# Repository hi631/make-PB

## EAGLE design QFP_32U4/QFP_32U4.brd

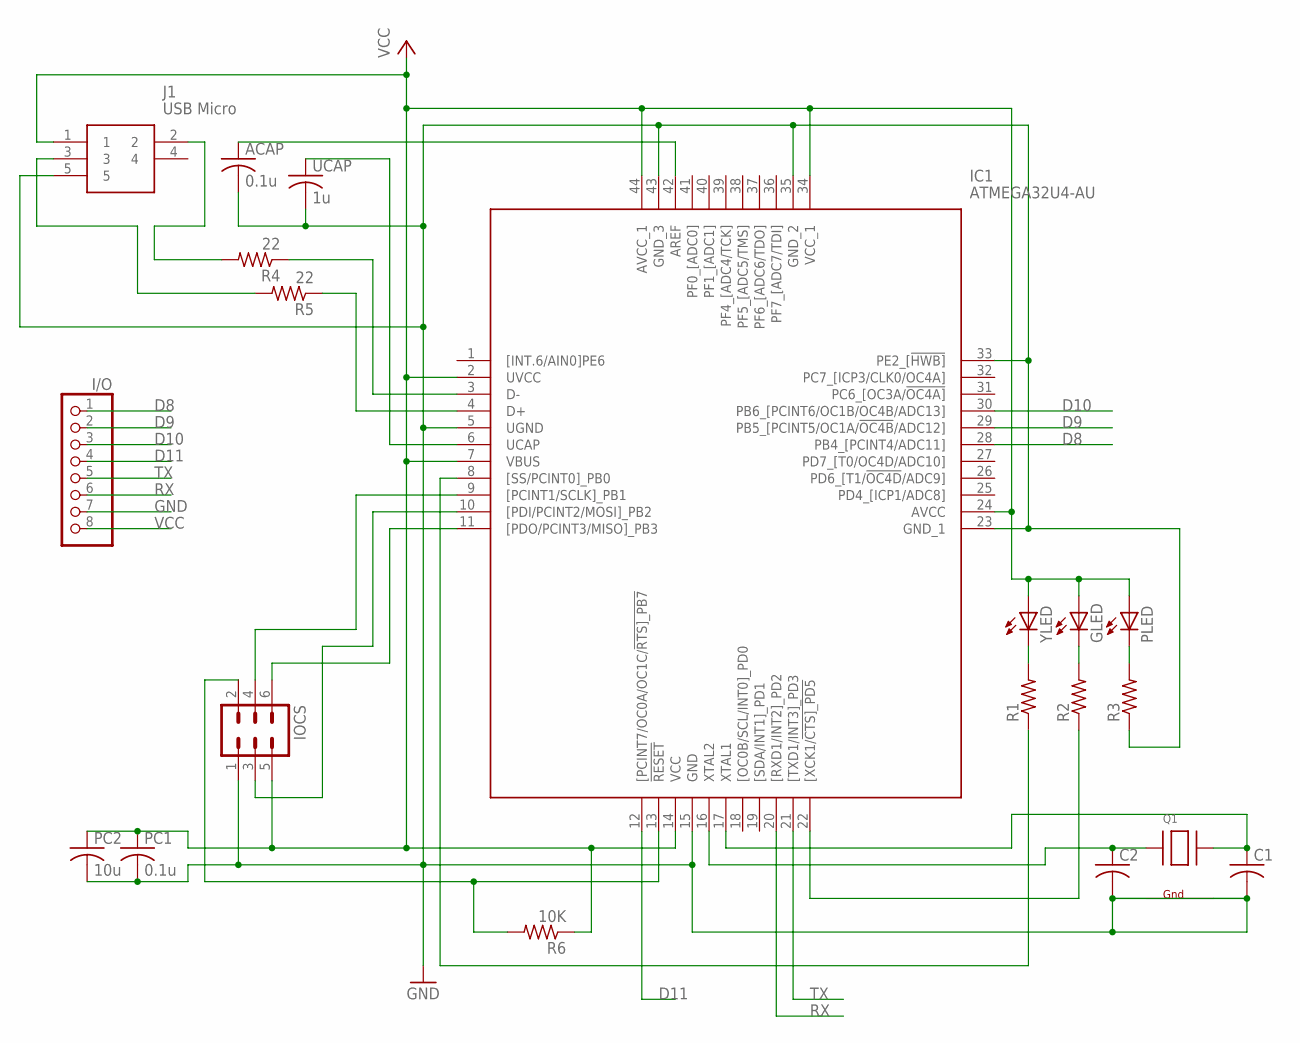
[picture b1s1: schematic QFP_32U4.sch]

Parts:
ACAP: 0.1u; C0805
C1, C2: C-USC0805; C0805
GLED: LEDCHIP-LED0805; CHIP-LED0805
I/O: PINHD-1X8CLEANBIG; 1X08-CLEANBIG
IC1: ATMEGA32U4-AU; QFP80P1200X1200X120-44N
IOCS: MA03-2
J1: USB Micro; 10104110-0001LF
PC1: 0.1u; C0805
PC2: 10u; C0805
PLED: LEDCHIP-LED0805; CHIP-LED0805
Q1: XTAL-4-3225; NX3225
R1, R2, R3: R-US_M0805; M0805
R4, R5: 22; M0805
R6: 10K; M0805
UCAP: 1u; C0805
YLED: LEDCHIP-LED0805; CHIP-LED0805

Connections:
D8: I/O.1, IC1.28 (PB4_[PCINT4/ADC11])
D9: I/O.2, IC1.29 (PB5_[PCINT5/OC1A/!OC4B!/ADC12])
D10: I/O.3, IC1.30 (PB6_[PCINT6/OC1B/OC4B/ADC13])
D11: I/O.4, IC1.12 ([PCINT7/OC0A/OC1C/!RTS]_PB7)
GND: ACAP.2, C1.2, C2.2, I/O.7, IC1.5 (UGND), IC1.15 (GND), IC1.23 (GND_1), IC1.33 (PE2_[!HWB]), IC1.35 (GND_2), IC1.43 (GND_3), IOCS.1, J1.5, PC1.2, PC2.2, Q1.2 (G2), Q1.4 (G1), R3.1, UCAP.2
unnamed: IC1.3 (D-), R4.1
unnamed: IC1.4 (D+), R5.1
unnamed: J1.2, R4.2
unnamed: IC1.6 (UCAP), UCAP.1
unnamed: R1.2, YLED.C
unnamed: IC1.8 ([SS/PCINT0]_PB0), R1.1
unnamed: IC1.9 ([PCINT1/SCLK]_PB1), IOCS.4
unnamed: IC1.10 ([PDI/PCINT2/MOSI]_PB2), IOCS.3
unnamed: IC1.11 ([PDO/PCINT3/MISO]_PB3), IOCS.6
unnamed: IC1.13 (!RESET), IOCS.2, R6.2
unnamed: J1.3, R5.2
unnamed: GLED.C, R2.2
unnamed: C2.1, IC1.16 (XTAL2), Q1.1 (X1)
unnamed: IC1.22 ([XCK1/!CTS]_PD5), R2.1
unnamed: PLED.C, R3.2
unnamed: C1.1, IC1.17 (XTAL1), Q1.3 (X2)
unnamed: ACAP.1, IC1.42 (AREF)
RX: I/O.6, IC1.20 ([RXD1/INT2]_PD2)
TX: I/O.5, IC1.21 ([TXD1/INT3]_PD3)
VCC: GLED.A, I/O.8, IC1.2 (UVCC), IC1.7 (VBUS), IC1.14 (VCC), IC1.24 (AVCC), IC1.34 (VCC_1), IC1.44 (AVCC_1), IOCS.5, J1.1, PC1.1, PC2.1, PLED.A, R6.1, YLED.A

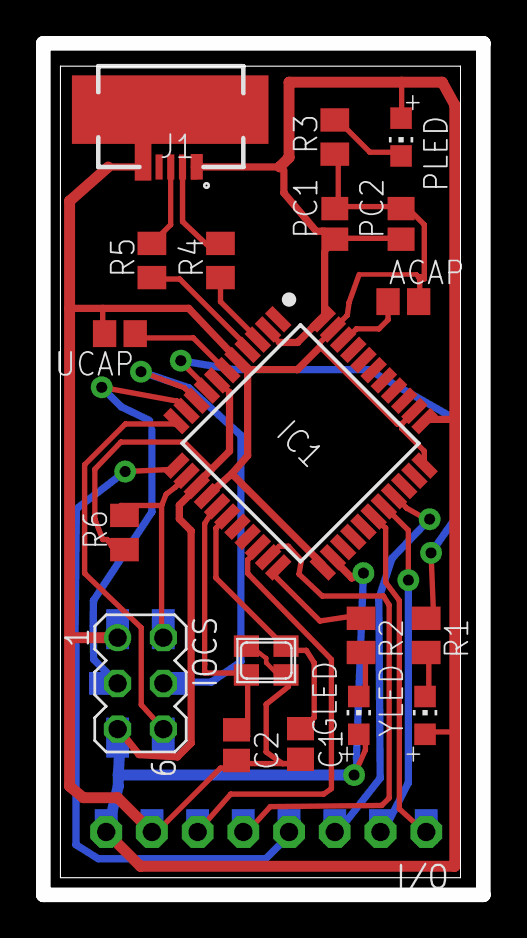
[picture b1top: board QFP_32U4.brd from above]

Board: 2 copper layers, 24.4 x 47.3 mm, 20 parts (0 on the bottom side), 25 nets.

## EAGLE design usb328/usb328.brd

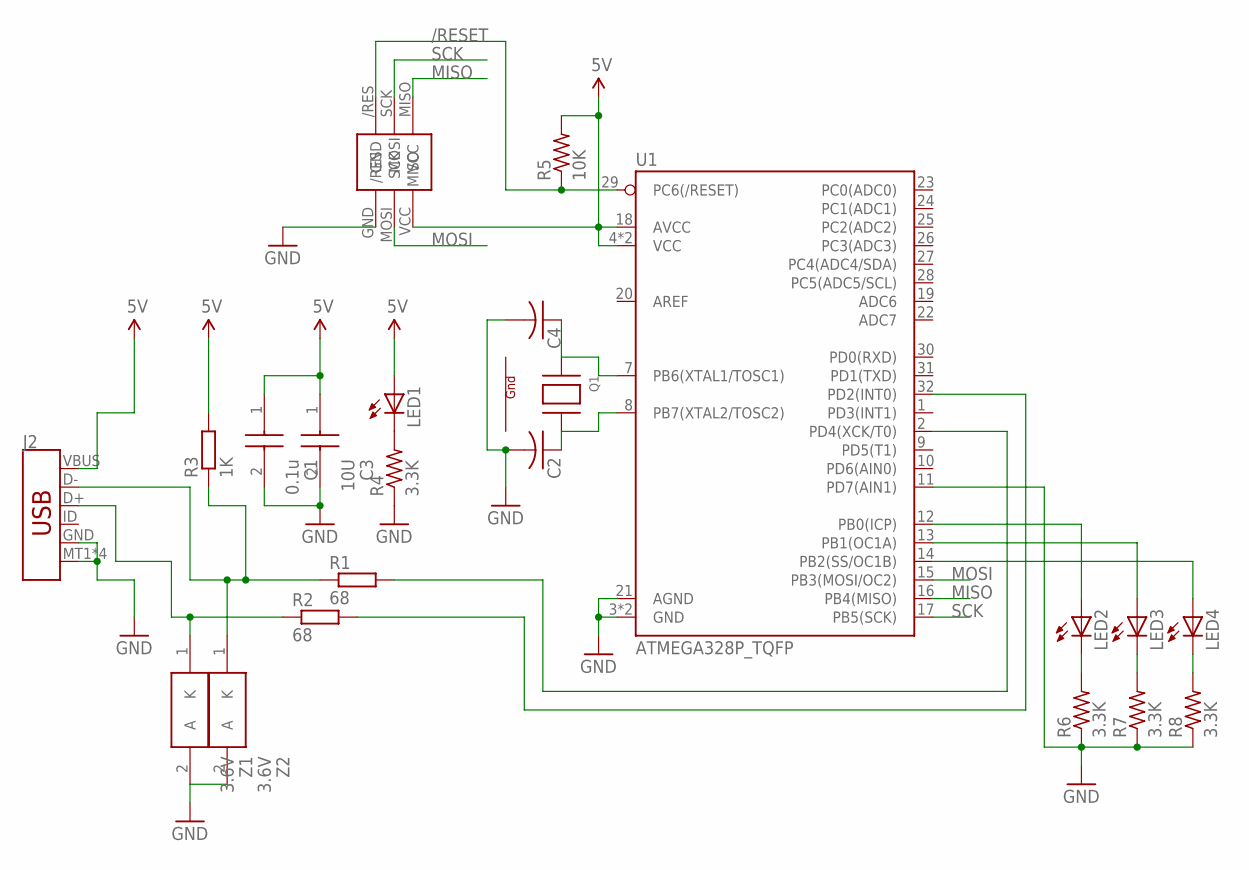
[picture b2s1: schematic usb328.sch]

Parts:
C1: 0.1u; CAPC2012X70N
C2, C4: C-USC0805; C0805
C3: 10U; CAPC2012X70N
J2: USB_MICRO-B_SMT; USB-MICROB
LED1, LED2, LED3, LED4: LEDCHIPLED_0805; CHIPLED_0805
Q1: XTAL-4-3225; NX3225
R1, R2: 68; R2012
R3: 1K; R2012
R4, R6, R7, R8: 3.3K; R0805
R5: 10K; R0805
U1: ATMEGA328P_TQFP; TQFP32-08
U$4: ICSP-E
Z1, Z2: 3.6V; TUM-D2

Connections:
5V: C1.1, C3.1, J2.VBUS, LED1.A, R3.2, R5.2, U1.4 (VCC), U1.6 (VCC), U1.18 (AVCC), U$4.VCC
/RESET: R5.1, U1.29 (PC6(/RESET)), U$4./RES
G1: Q1.4 (G1)
G2: Q1.2 (G2)
GND: C1.2, C2.2, C3.2, C4.2, J2.GND, J2.MT1 (SHIELD), J2.MT2 (SHIELD), J2.P$1 (SHIELD), J2.P$2 (SHIELD), R4.1, R6.1, R7.1, R8.1, U1.3 (GND), U1.5 (GND), U1.11 (PD7(AIN1)), U1.21 (AGND), U$4.GND, Z1.2 (A), Z2.2 (A)
MISO: U1.16 (PB4(MISO)), U$4.MISO
MOSI: U1.15 (PB3(MOSI/OC2)), U$4.MOSI
unnamed: R1.2, U1.2 (PD4(XCK/T0))
unnamed: R2.2, U1.32 (PD2(INT0))
unnamed: C4.1, Q1.1 (X1), U1.7 (PB6(XTAL1/TOSC1))
unnamed: C2.1, Q1.3 (X2), U1.8 (PB7(XTAL2/TOSC2))
unnamed: LED1.C, R4.2
unnamed: LED2.A, U1.12 (PB0(ICP))
unnamed: LED3.A, U1.13 (PB1(OC1A))
unnamed: LED2.C, R6.2
unnamed: LED3.C, R7.2
unnamed: J2.D-, R1.1, R3.1, Z2.1 (K)
unnamed: J2.D+, R2.1, Z1.1 (K)
unnamed: LED4.A, U1.14 (PB2(SS/OC1B))
unnamed: LED4.C, R8.2
SCK: U1.17 (PB5(SCK)), U$4.SCK

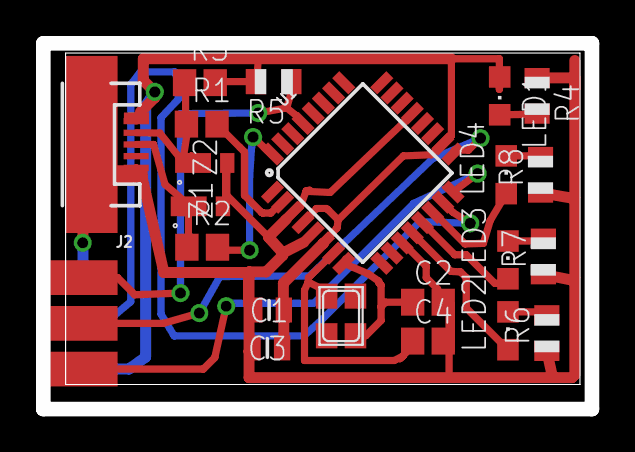
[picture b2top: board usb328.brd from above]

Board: 2 copper layers, 30.5 x 20.3 mm, 22 parts (0 on the bottom side), 19 nets.

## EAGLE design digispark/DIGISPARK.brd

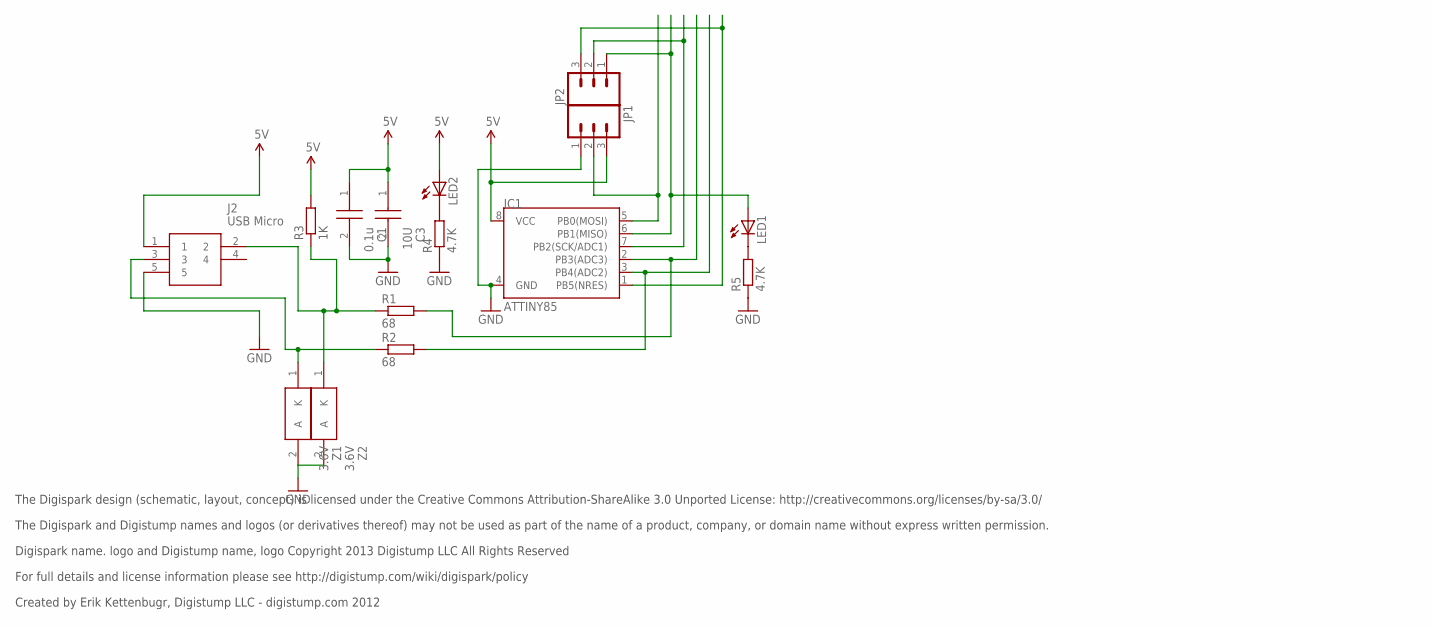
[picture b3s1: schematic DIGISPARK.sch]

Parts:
C1: 0.1u; CAPC2012X70N
C3: 10U; CAPC2012X70N
IC1: ATTINY85; SO08-EIAJ
J2: USB Micro; 10104110-0001LF
JP1, JP2: M03PTH; 1X03
LED1, LED2: LEDCHIPLED_0805; CHIPLED_0805
R1, R2: 68; R2012
R3: 1K; R2012
R4, R5: 4.7K; R2012
Z1, Z2: 3.6V; TUM-D2

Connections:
5V: C1.1, C3.1, IC1.8 (VCC), J2.1, JP1.3, LED2.A, R3.2
GND: C1.2, C3.2, IC1.4 (GND), J2.5, JP1.1, R4.1, R5.1, Z1.2 (A), Z2.2 (A)
unnamed: IC1.2 (PB3(ADC3)), R1.2
unnamed: IC1.6 (PB1(MISO)), JP2.1, LED1.A
unnamed: IC1.5 (PB0(MOSI)), JP1.2
unnamed: LED1.C, R5.2
unnamed: IC1.7 (PB2(SCK/ADC1)), JP2.2
unnamed: IC1.3 (PB4(ADC2)), R2.2
unnamed: LED2.C, R4.2
unnamed: IC1.1 (PB5(NRES)), JP2.3
unnamed: J2.2, R1.1, R3.1, Z2.1 (K)
unnamed: J2.3, R2.1, Z1.1 (K)

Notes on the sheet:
The Digispark design (schematic, layout, concept) is licensed under the Creative Commons Attribution-ShareAlike 3.0 Unported License: http://creativecommons.org/licenses/by-sa/3.0/
The Digispark and Digistump names and logos (or derivatives thereof) may not be used as part of the name of a product, company, or domain name without express written permission.
Digispark name. logo and Digistump name, logo Copyright 2013 Digistump LLC All Rights Reserved
For full details and license information please see http://digistump.com/wiki/digispark/policy
Created by Erik Kettenbugr, Digistump LLC - digistump.com 2012

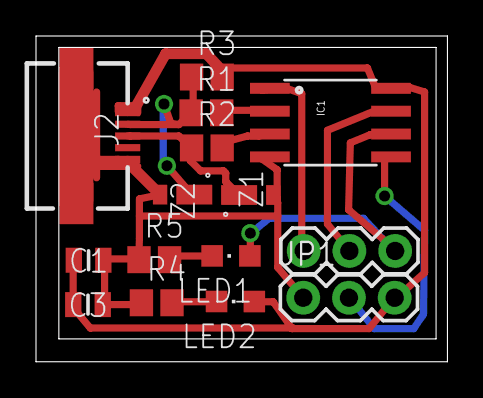
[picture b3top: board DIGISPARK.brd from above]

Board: 2 copper layers, 22.9 x 18.1 mm, 15 parts (0 on the bottom side), 12 nets.

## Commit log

2018-11-07 test
2026-06-13 new 2026/06/13

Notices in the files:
parts and their libraries:
SparkFun: Licensing: CC v3.0 Share-Alike You are welcome to use this library for commercial purposes.
SparkFun-Connectors: Licensing: Creative Commons ShareAlike 4.0 International - https://creativecommons.org/licenses/by-sa/4.0
